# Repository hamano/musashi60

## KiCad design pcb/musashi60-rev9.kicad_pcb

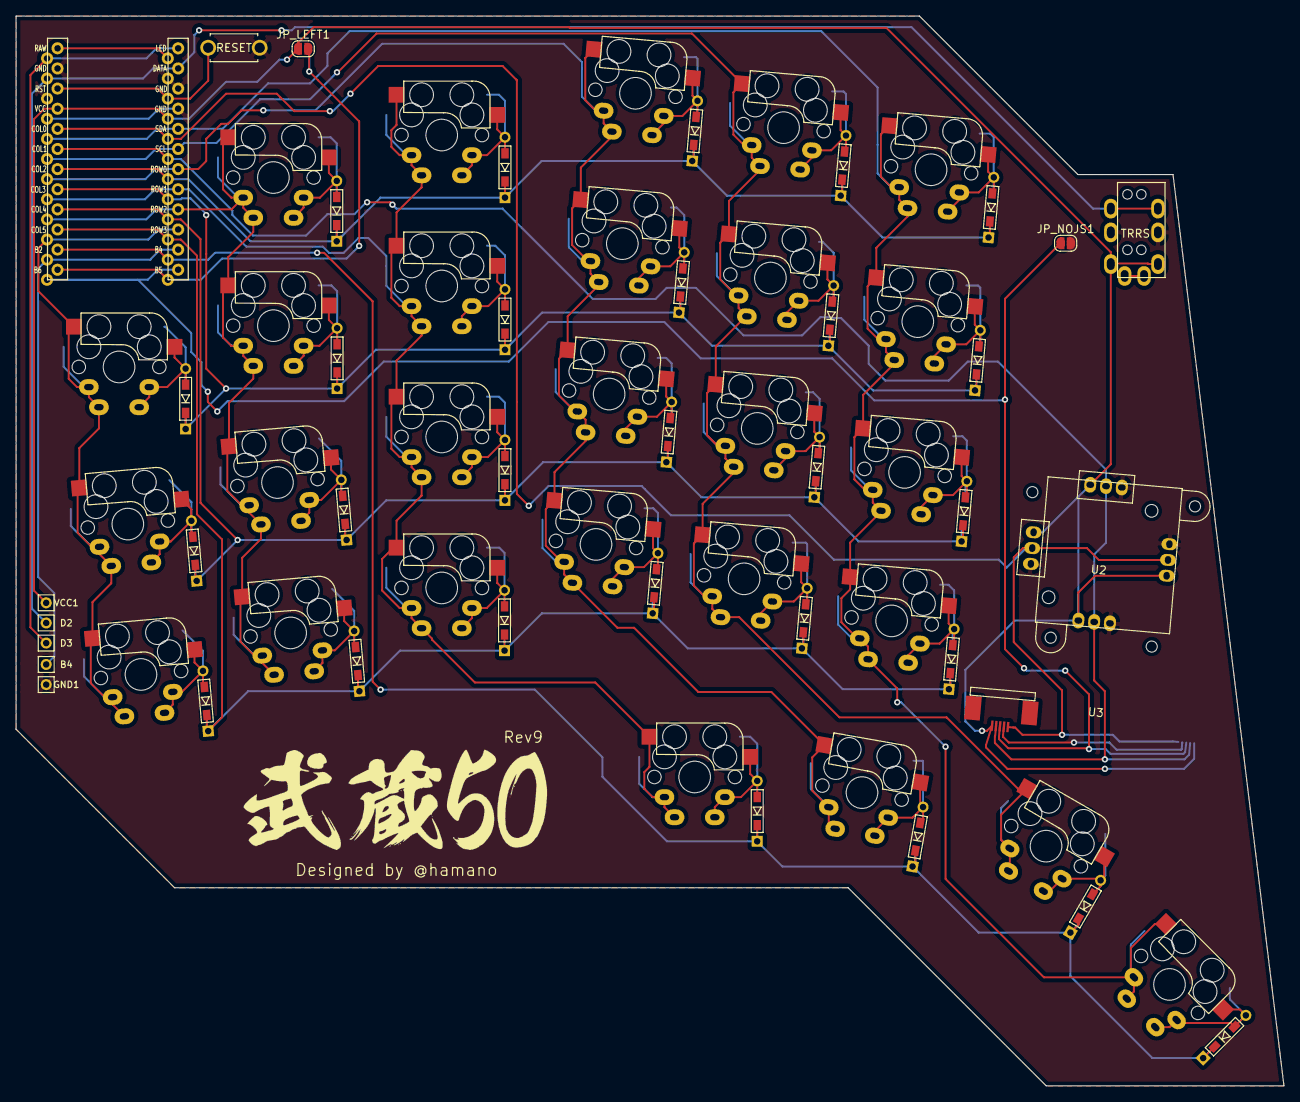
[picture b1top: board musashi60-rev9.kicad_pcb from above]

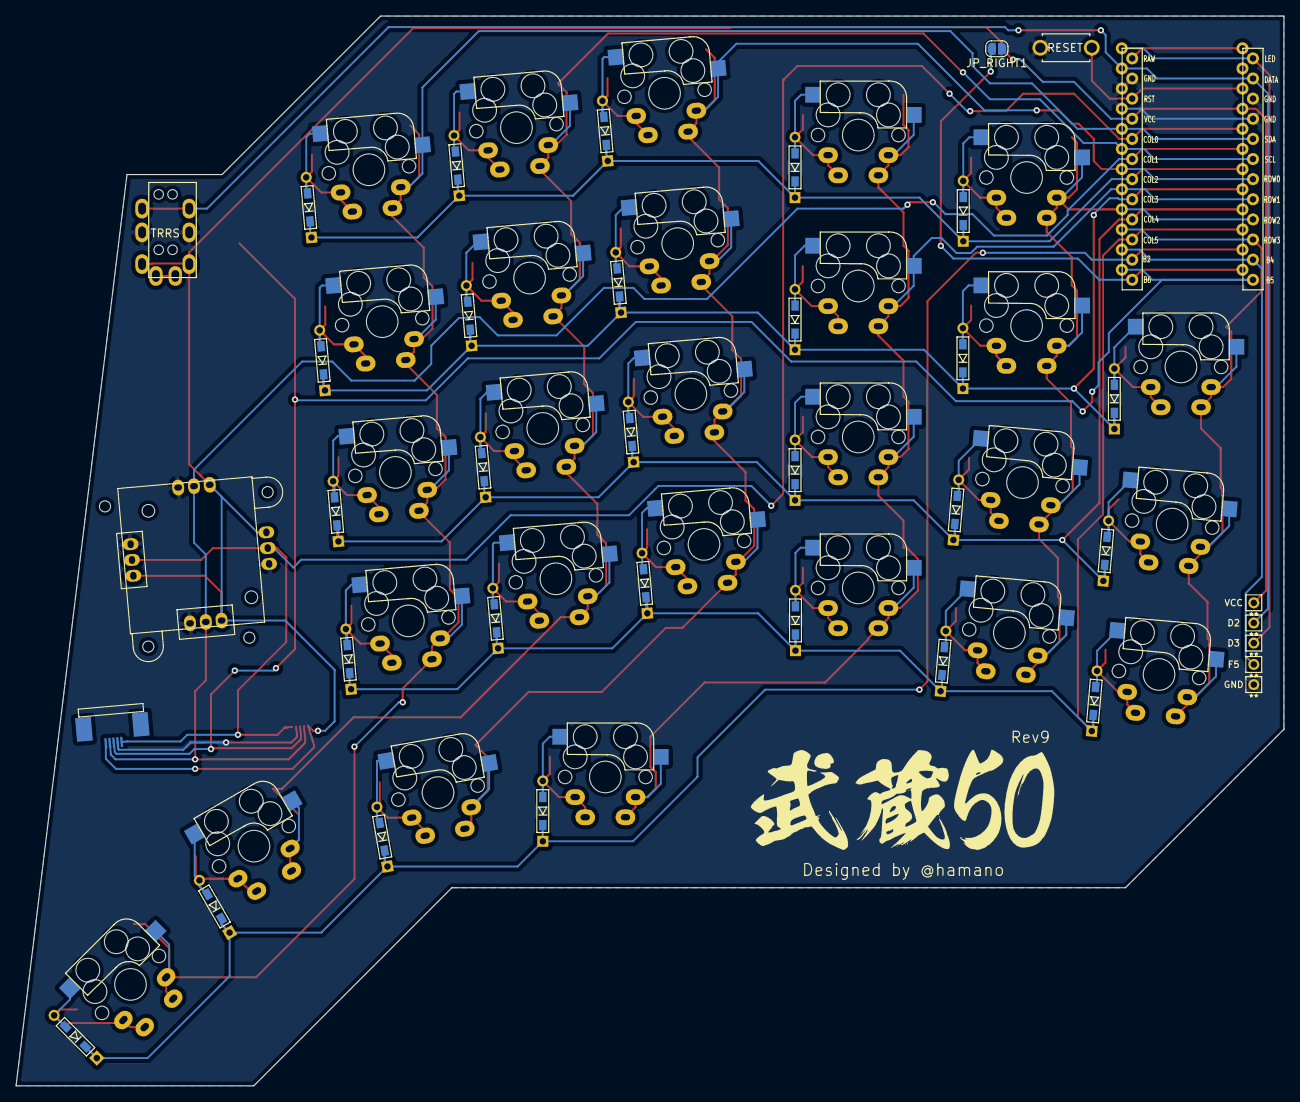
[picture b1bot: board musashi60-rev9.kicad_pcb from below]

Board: 2 copper layers, 160.0 x 135.0 mm, 69 parts (2 on the bottom side), 48 nets.

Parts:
B4: MountingHole_Pad; 1pin_conn
D2, D3: MountingHole_Pad; 1pin_conn
D_A1, D_A2, D_A3, D_A4, D_A5: D; D3_TH_SMD
D_B1, D_B2, D_B3, D_B4, D_B5: D; D3_TH_SMD
D_C1, D_C2, D_C3, D_C4, D_C5: D; D3_TH_SMD
D_D1, D_D2, D_D3, D_D4, D_D5: D; D3_TH_SMD
D_E1, D_E2, D_E3, D_E4: D; D3_TH_SMD
D_F2, D_F3, D_F4: D; D3_TH_SMD
GND1: MountingHole_Pad; 1pin_conn
G_LOGO_B: LOGO; musashi50-silk-256
G_LOGO_F: LOGO; musashi50-silk-256
J1: MJ-4PP-9
JP_LEFT1: Jumper; SolderJumper-2_P1.3mm_Open_RoundedPad1.0x1.5mm
JP_NOJS1: Jumper; SolderJumper-2_P1.3mm_Open_RoundedPad1.0x1.5mm
JP_RIGHT1: Jumper; SolderJumper-2_P1.3mm_Open_RoundedPad1.0x1.5mm
SW_A1, SW_A2, SW_A3, SW_A4, SW_A5: SW_PUSH; CherryMX_Direct_Hotswap_Reversible
SW_B1, SW_B2, SW_B3, SW_B4, SW_B5: SW_PUSH; CherryMX_Direct_Hotswap_Reversible
SW_C1, SW_C2, SW_C3, SW_C4, SW_C5: SW_PUSH; CherryMX_Direct_Hotswap_Reversible
SW_D1, SW_D2, SW_D3, SW_D4, SW_D5: SW_PUSH; CherryMX_Direct_Hotswap_Reversible
SW_E1, SW_E2, SW_E3, SW_E4: SW_PUSH; CherryMX_Direct_Hotswap_Reversible
SW_F2, SW_F3, SW_F4: SW_PUSH; CherryMX_Direct_Hotswap_Reversible
SW_RST1: SW_PUSH; ResetSW
U1: ProMicro_r; ProMicro_v2
U2: joystick; J08K
U3: joystick_s; Joycon_Stick
VCC1: MountingHole_Pad; 1pin_conn

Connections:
B1: D_A3.1, D_B3.1, D_C3.1, D_D3.1, D_E3.1, D_F3.1, U1.16
B2: D_A5.1, D_B5.1, D_C5.1, D_D5.1, U1.14
B3: D_A4.1, D_B4.1, D_C4.1, D_D4.1, D_E4.1, D_F4.1, U1.15
B4: B4.1, U1.11
B5: JP_NOJS1.1, U1.12, U3.3
B6: JP_LEFT1.2, JP_RIGHT1.2, U1.13
C6: SW_D1.1, SW_D2.1, SW_D3.1, SW_D4.1, SW_D5.1, U1.8
D0: SW_B1.1, SW_B2.1, SW_B3.1, SW_B4.1, SW_B5.1, U1.6
D1: SW_A1.1, SW_A2.1, SW_A3.1, SW_A4.1, SW_A5.1, U1.5
D2: D2.1, J1.B, U1.2
D3: D3.1, U1.1
D4: SW_C1.1, SW_C2.1, SW_C3.1, SW_C4.1, SW_C5.1, U1.7
D7: SW_E1.1, SW_E2.1, SW_E3.1, SW_E4.1, U1.9
E6: SW_F2.1, SW_F3.1, SW_F4.1, U1.10
F4: U1.20, U2.3, U3.5
F5: U1.19, U2.4, U3.2
F6: D_A1.1, D_B1.1, D_C1.1, D_D1.1, D_E1.1, U1.18
F7: D_A2.1, D_B2.1, D_C2.1, D_D2.1, D_E2.1, D_F2.1, U1.17
GND: GND1.1, J1.C, JP_NOJS1.2, JP_RIGHT1.1, SW_RST1.1, U1.3, U1.4, U1.23, U2.2, U3.4
unnamed: D_A1.2, SW_A1.2
unnamed: D_A2.2, SW_A2.2
unnamed: D_A3.2, SW_A3.2
unnamed: D_A4.2, SW_A4.2
unnamed: D_A5.2, SW_A5.2
unnamed: D_B1.2, SW_B1.2
unnamed: D_B2.2, SW_B2.2
unnamed: D_B3.2, SW_B3.2
unnamed: D_B4.2, SW_B4.2
unnamed: D_B5.2, SW_B5.2
unnamed: D_C1.2, SW_C1.2
unnamed: D_C2.2, SW_C2.2
unnamed: D_C3.2, SW_C3.2
unnamed: D_C4.2, SW_C4.2
unnamed: D_C5.2, SW_C5.2
unnamed: D_D1.2, SW_D1.2
unnamed: D_D2.2, SW_D2.2
unnamed: D_D3.2, SW_D3.2
unnamed: D_D4.2, SW_D4.2
unnamed: D_D5.2, SW_D5.2
unnamed: D_E1.2, SW_E1.2
unnamed: D_E2.2, SW_E2.2
unnamed: D_E3.2, SW_E3.2
unnamed: D_E4.2, SW_E4.2
unnamed: D_F2.2, SW_F2.2
unnamed: D_F3.2, SW_F3.2
unnamed: D_F4.2, SW_F4.2
RST: SW_RST1.2, U1.22
VCC: J1.D, JP_LEFT1.1, U1.21, U2.1, U3.1, VCC1.1
